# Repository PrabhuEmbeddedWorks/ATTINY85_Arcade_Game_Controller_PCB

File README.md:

# ATTINY85 Arcade Game Controller PCB

## Features
- ATtiny85 microcontroller based embedded system
- 0.96 inch SSD1306 I2C OLED display
- Three push buttons for game control (Left, Right, Jump/Fire)
- Buzzer for audio feedback
- CR2032 coin cell battery powered
- Slide switch for power control
- Custom controller shaped PCB outline
- 3D PCB visualization using KiCad
- Custom KiCad footprint library
- Autorouting using FreeRouting plugin

## Tools and Technologies

| Tool | Purpose |
|-----|--------|
| KiCad 8.0 | Schematic design and PCB layout |
| FreeRouting Plugin | Autorouting of PCB tracks |
| Java JRE | Runtime required for FreeRouting |
| Inkscape | Creating custom PCB outline (DXF import) |

## System Architecture

The system is organized into four functional modules.

### Power Management

The system is powered using a CR2032 coin cell battery. A slide switch is used to control power to the board, and an LED indicator provides visual confirmation that the system is powered.

### Microcontroller

The ATtiny85 microcontroller serves as the central processing unit of the system. It handles button input processing, OLED display communication, buzzer control, and execution of the game logic.

### Display Interface

The display module used in the project is a 0.96 inch SSD1306 OLED. Communication between the display and the ATtiny85 is implemented using the I2C protocol. This allows the system to control the display using only two communication lines: SDA and SCL.

### Input Controls

Three push buttons are used as user inputs:

- LEFT button
- RIGHT button
- JUMP/FIRE button

Each button uses a pull-down resistor to ensure a stable logic level when the button is not pressed.

### Audio Output

A small buzzer is connected to the microcontroller to provide sound feedback during gameplay.

### Programming Interface

A programming header is included to allow firmware programming of the ATtiny85 using an ISP programmer.

## PCB Design

The PCB layout was created using KiCad 8.0. A custom controller-shaped outline was designed by importing a DXF graphic into the Edge.Cuts layer.

Component placement was optimized for usability and routing efficiency:

- OLED display positioned at the top center
- Control buttons placed along the top edges
- ATtiny85 microcontroller positioned in the lower section
- Buzzer placed centrally for balanced layout
- Coin cell battery holder placed on the backside of the PCB

Signal routing was performed using KiCad’s interactive router, and automated routing was also tested using the FreeRouting plugin.

## Custom Component Libraries

Several components used in the project were not available in the default KiCad libraries. Custom footprints were created for the following components:

- SSD1306 OLED display module
- CR2032 battery holder
- SS-12D00 slide switch

Footprint and 3D model integration involved the use of the following file formats:

- `.kicad_mod` for PCB footprints
- `.wrl` and `.step` for 3D models

3D model alignment was achieved by adjusting rotation and offset parameters within the KiCad footprint editor.

## 3D PCB Visualization

KiCad’s 3D viewer was used to validate mechanical alignment and component placement. This allowed verification of OLED placement, switch orientation, battery holder position, and overall board structure before manufacturing.

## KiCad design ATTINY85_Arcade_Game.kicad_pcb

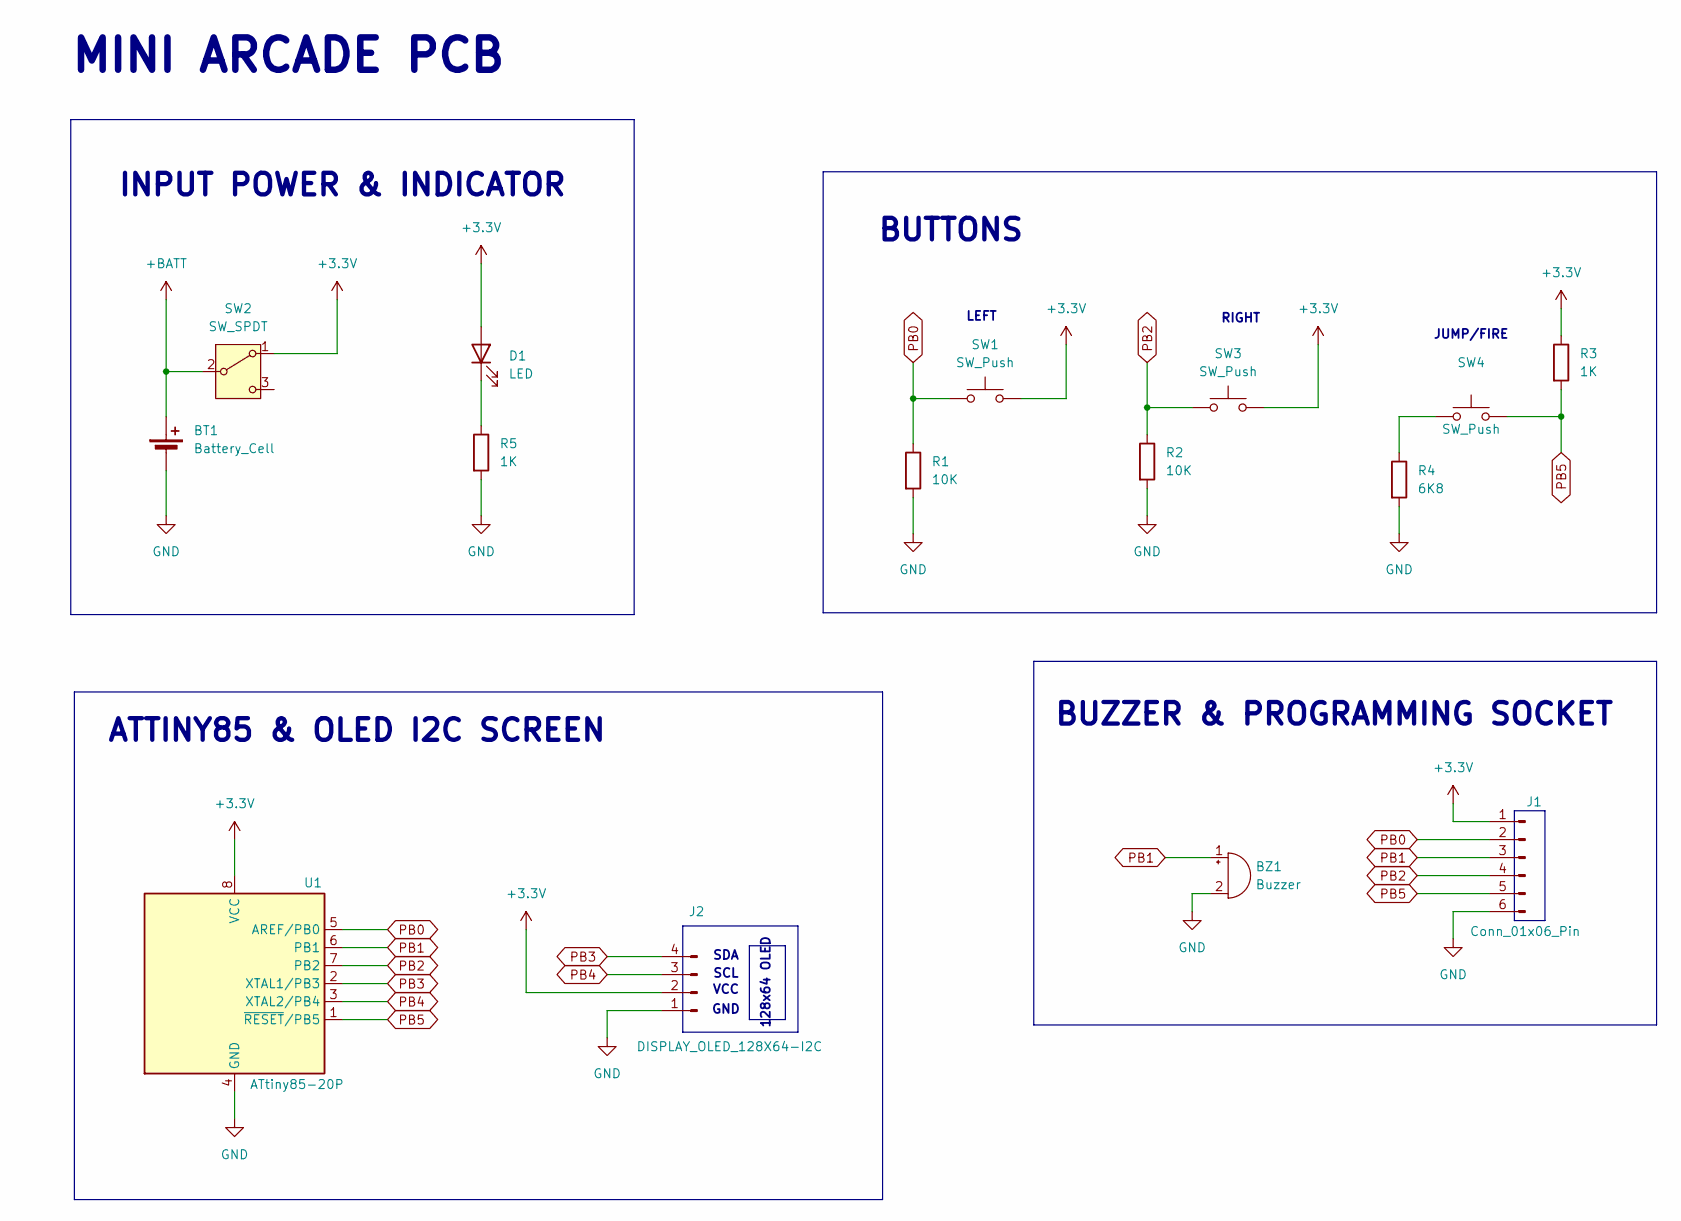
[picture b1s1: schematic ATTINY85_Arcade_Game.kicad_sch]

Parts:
BT1: Battery_Cell; BatteryHolder_Keystone_104_1x23mm
BZ1: Buzzer; MagneticBuzzer_ProSignal_ABT-410-RC
D1: LED; LED_0805_2012Metric
J1: Conn_01x06_Pin; PinSocket_1x06_P2.54mm_Vertical
J2: DISPLAY_OLED_128X64-I2C; MODULE_DM-OLED096-636
R1: 10K; R_Axial_DIN0207_L6.3mm_D2.5mm_P7.62mm_Horizontal
R2: 10K; R_Axial_DIN0207_L6.3mm_D2.5mm_P10.16mm_Horizontal
R3: 1K; R_Axial_DIN0207_L6.3mm_D2.5mm_P10.16mm_Horizontal
R4: 6K8; R_Axial_DIN0207_L6.3mm_D2.5mm_P10.16mm_Horizontal
R5: 1K; R_0805_2012Metric
SW1, SW3, SW4: SW_Push; SW_PUSH_6mm_H5mm
SW2: SW_SPDT; SS_12D00
U1: ATtiny85-20P; DIP-8_W7.62mm

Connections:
+3.3V: D1.2 (A), J1.1, J2.2, R3.1, SW1.2, SW2.1 (A), SW3.2, U1.8 (VCC)
+BATT: BT1.1 (+), SW2.2 (B)
GND: BT1.2 (-), BZ1.2 (-), J1.6, J2.1, R1.2, R2.2, R4.2, R5.2, U1.4 (GND)
unnamed: D1.1 (K), R5.1
unnamed: R4.1, SW4.1
PB0: J1.2, R1.1, SW1.1, U1.5 (AREF/PB0)
PB1: BZ1.1 (+), J1.3, U1.6 (PB1)
PB2: J1.4, R2.1, SW3.1, U1.7 (PB2)
PB3: J2.4, U1.2 (XTAL1/PB3)
PB4: J2.3, U1.3 (XTAL2/PB4)
PB5: J1.5, R3.2, SW4.2, U1.1 (~RESET/PB5)

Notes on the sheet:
MINI ARCADE PCB
LEFT
INPUT POWER & INDICATOR
GND
VCC
SCL
RIGHT
SDA
BUZZER & PROGRAMMING SOCKET
128x64 OLED
ATTINY85 & OLED I2C SCREEN
BUTTONS
JUMP/FIRE

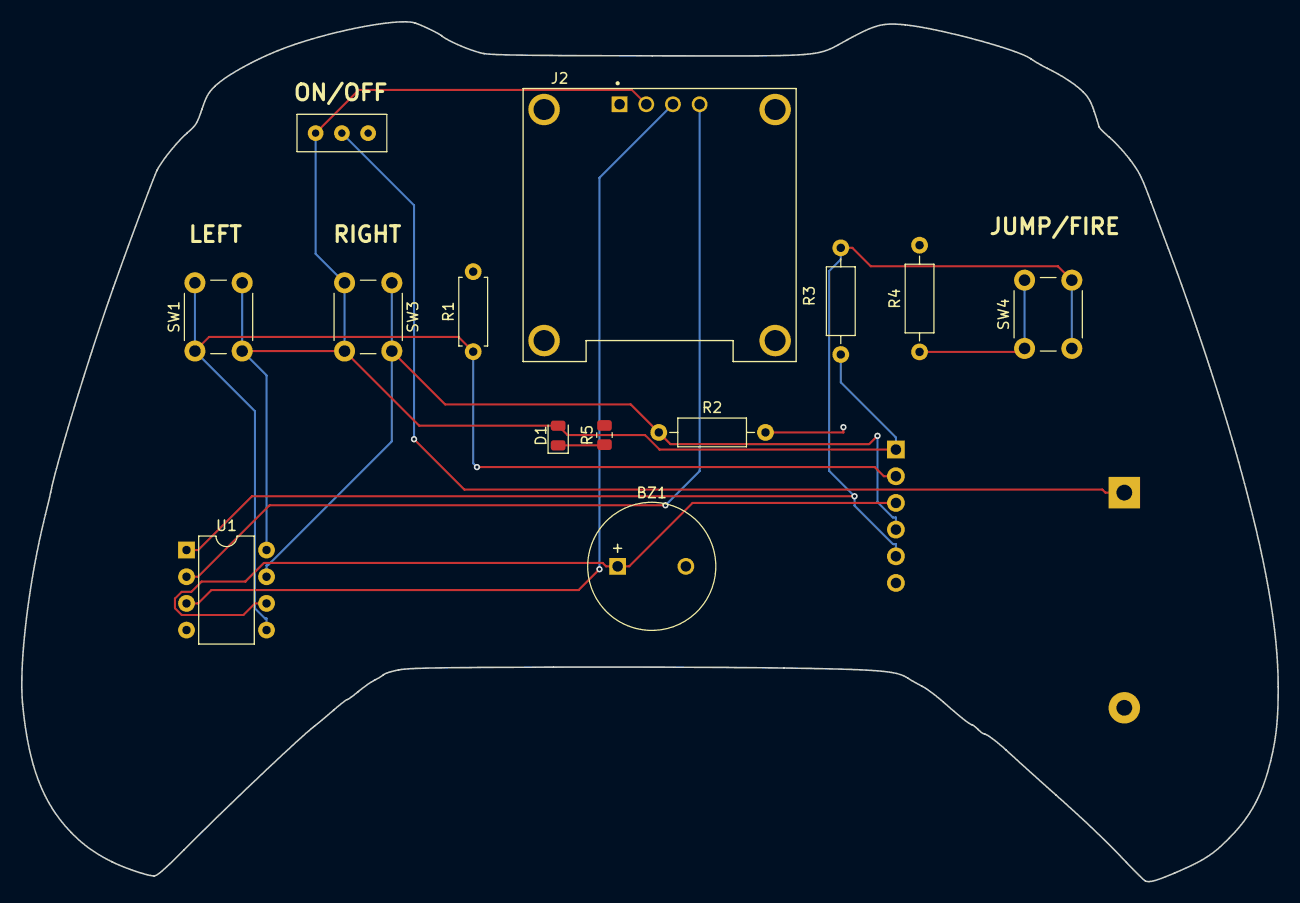
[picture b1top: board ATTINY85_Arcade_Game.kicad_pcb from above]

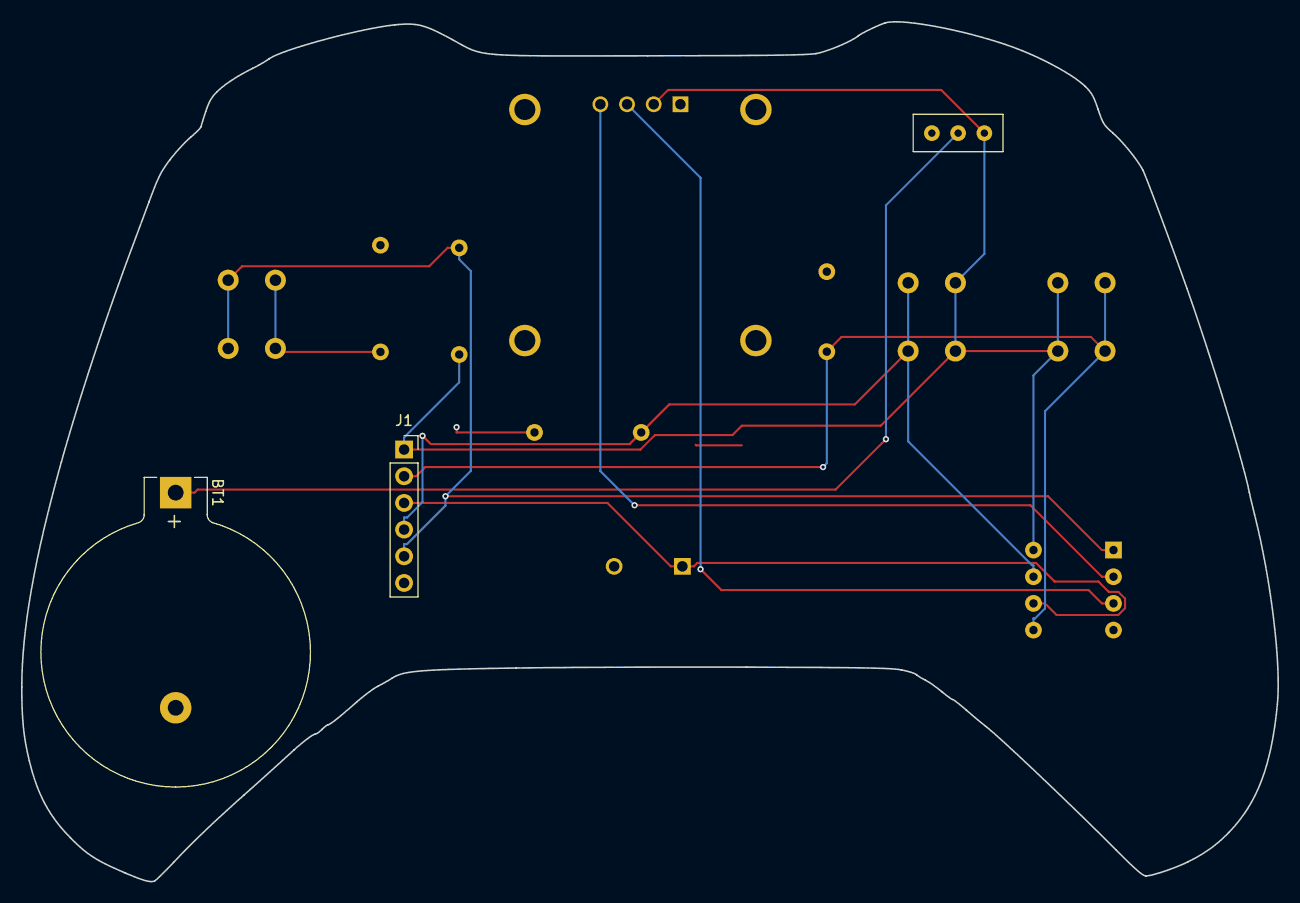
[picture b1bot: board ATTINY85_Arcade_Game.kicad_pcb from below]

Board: 2 copper layers, 119.6 x 81.9 mm, 15 parts (2 on the bottom side), 11 nets.

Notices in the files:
parts and their libraries:
Mini power slide switch – Licensed under CC-BY-SA-4.0 (based on https://github.com/kaibader/KiCad-Library)
